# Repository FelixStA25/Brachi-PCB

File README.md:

Main PCB for brachi\n
File named kicad is a mess

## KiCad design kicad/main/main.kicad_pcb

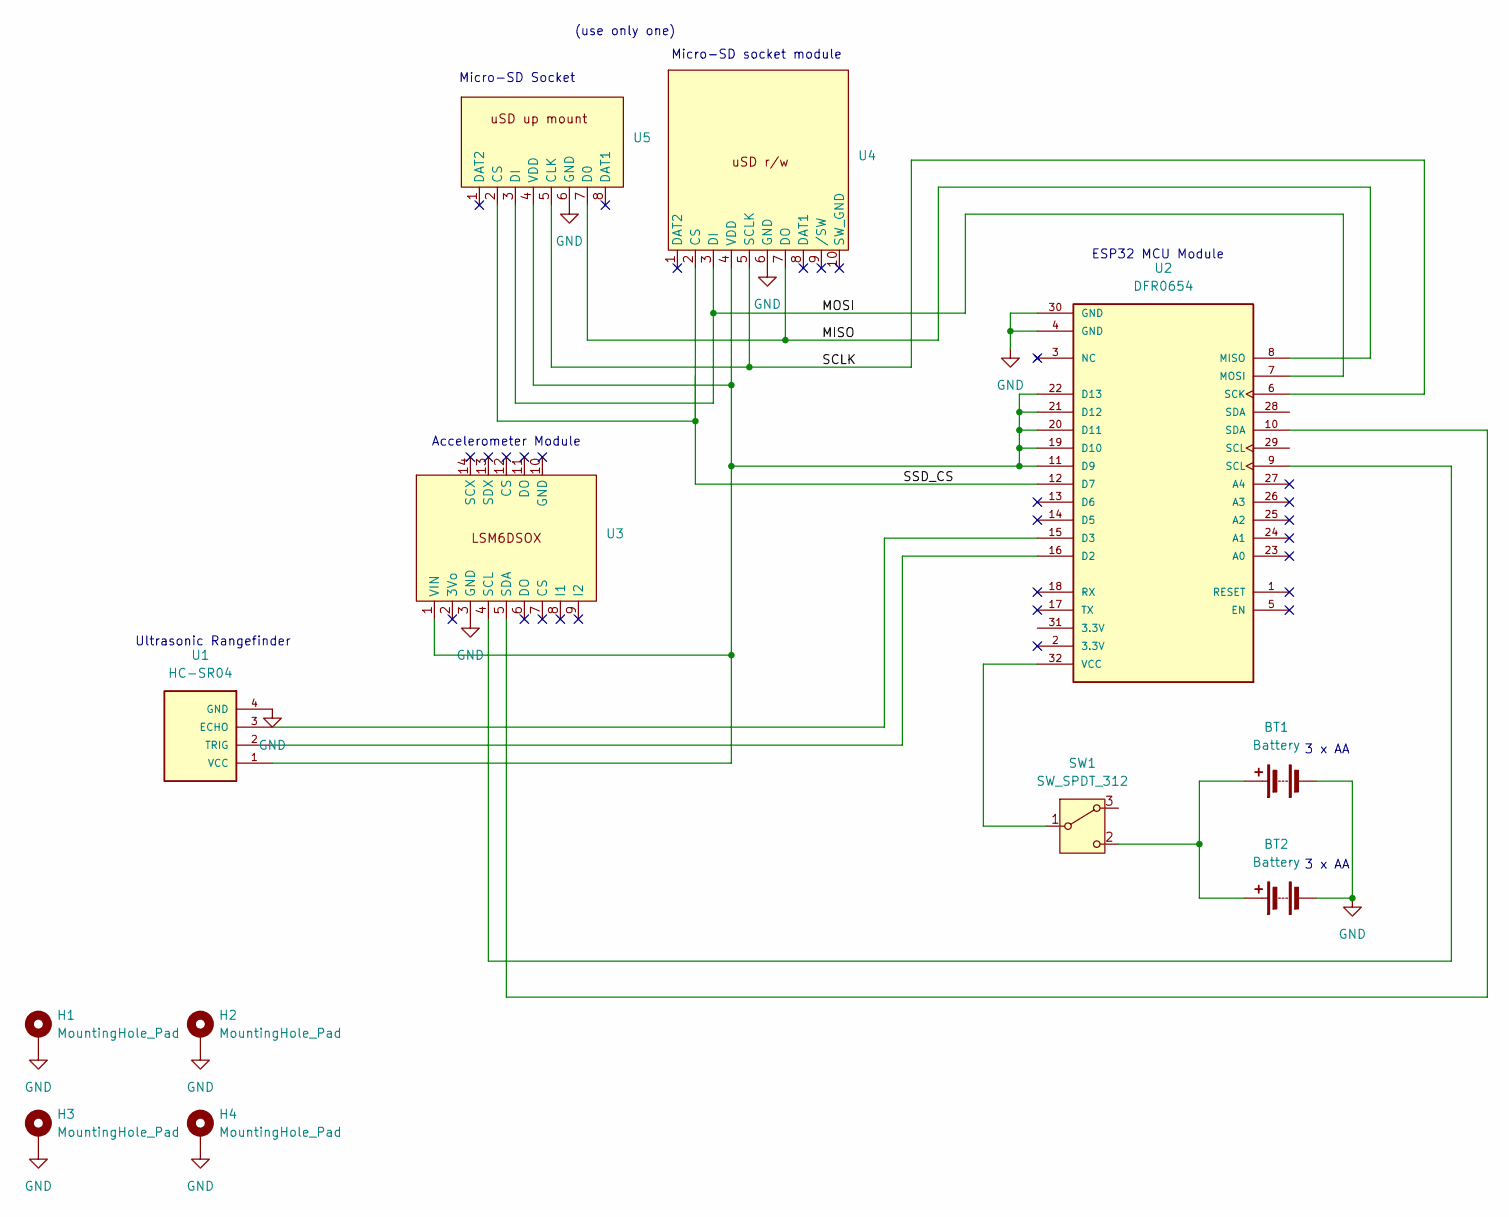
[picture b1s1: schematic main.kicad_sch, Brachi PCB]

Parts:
BT1, BT2: Battery; PinHeader_1x02_P2.54mm_Vertical
H1, H2, H3, H4: MountingHole_Pad; MountingHole_3.2mm_M3_DIN965_Pad
SW1: SW_SPDT_312; switch_sp
U1: HC-SR04; XCVR_HC-SR04
U2: DFR0654; MODULE_DFR0654
U3: accelerometer
U4: uSD board
U5: uSD mount (up)

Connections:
/MISO: U2.8 (MISO), U4.7 (DO), U5.7 (D0)
/MOSI: U2.7 (MOSI), U4.3 (DI), U5.3 (DI)
/SCLK: U2.6 (SCK), U4.5 (SCLK), U5.5 (CLK)
/SSD_CS: U2.12 (D7), U4.2 (CS), U5.2 (CS)
GND: BT1.2 (-), BT2.2 (-), H1.1, H2.1, H3.1, H4.1, U1.4 (GND), U2.4 (GND), U2.30 (GND), U3.3 (GND), U4.6 (GND), U5.6 (GND)
unnamed: BT1.1 (+), BT2.1 (+), SW1.2 (C)
unnamed: SW1.1 (B), U2.32 (VCC)
unnamed: U1.3 (ECHO), U2.15 (D3)
unnamed: U1.2 (TRIG), U2.16 (D2)
unnamed: U1.1 (VCC), U2.11 (D9), U2.19 (D10), U2.20 (D11), U2.21 (D12), U2.22 (D13), U3.1 (VIN), U4.4 (VDD), U5.4 (VDD)
unnamed: U2.9 (SCL), U3.4 (SCL)
unnamed: U2.10 (SDA), U3.5 (SDA)

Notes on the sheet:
Micro-SD socket module
ESP32 MCU Module
3 x AA
(use only one)
Micro-SD Socket
Ultrasonic Rangefinder
Accelerometer Module

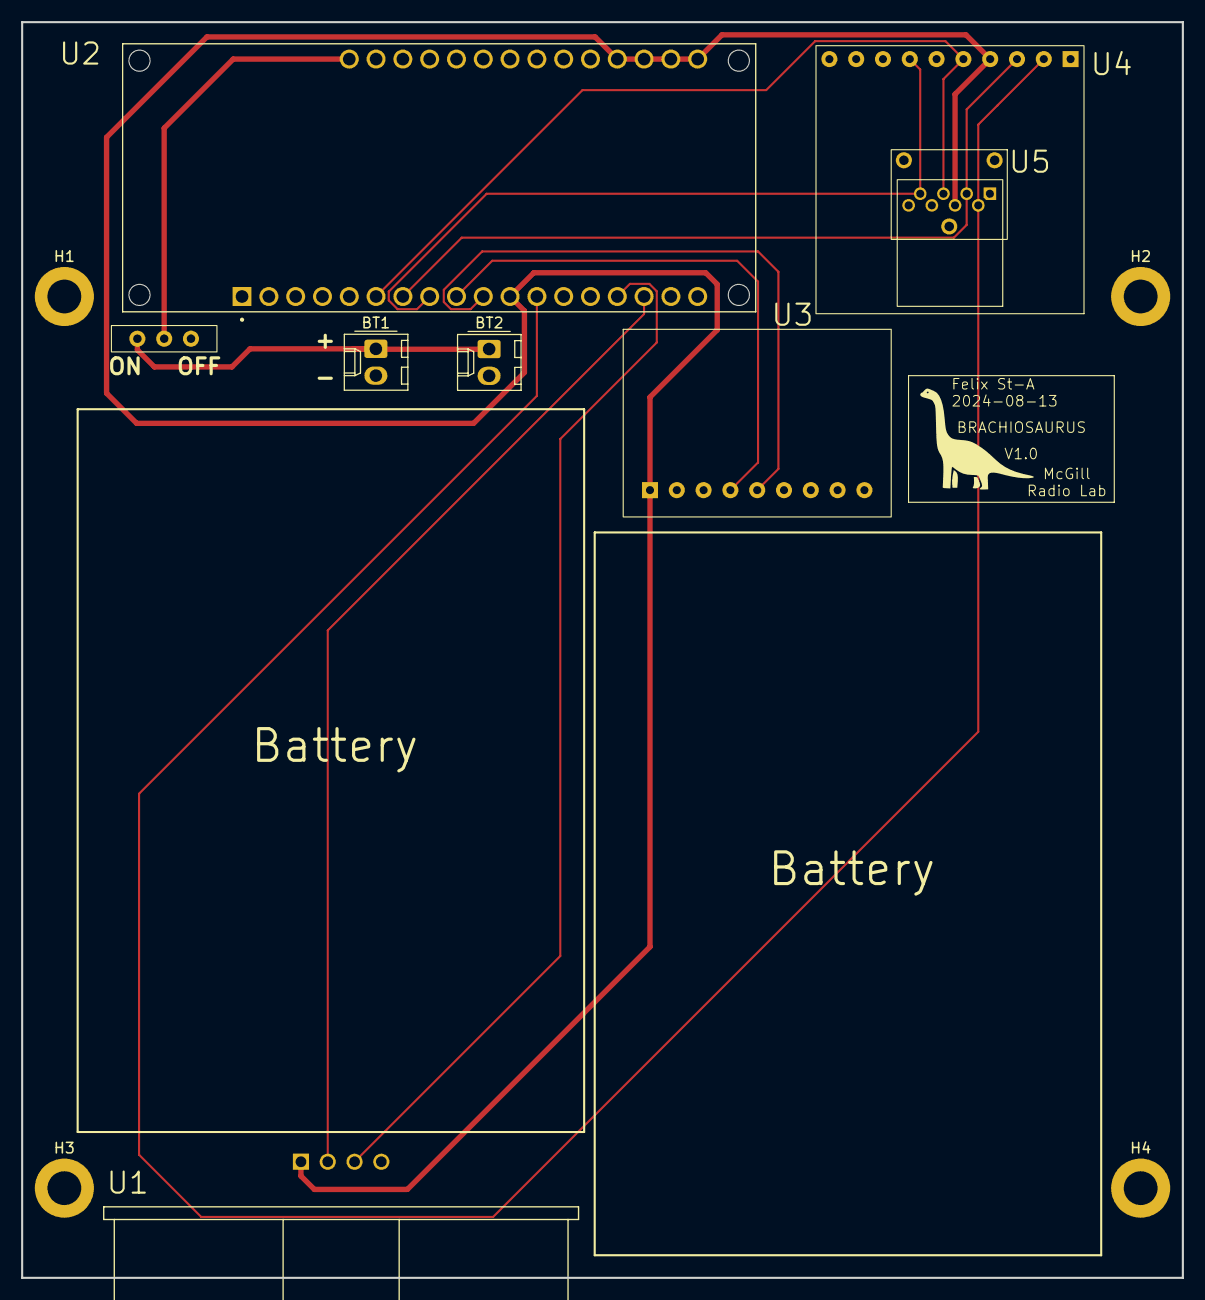
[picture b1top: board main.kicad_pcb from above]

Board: 2 copper layers, 110.0 x 119.0 mm, 12 parts (0 on the bottom side), 12 nets.

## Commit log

2024-08-13 cleaned up PCB design
2024-08-14 added mounting holes?
2024-08-14 add gitignore
2024-08-14 as sent to PCBWay
